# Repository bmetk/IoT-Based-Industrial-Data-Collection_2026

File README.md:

# COMPACT-MAPS
Machine Analizator and Processor System

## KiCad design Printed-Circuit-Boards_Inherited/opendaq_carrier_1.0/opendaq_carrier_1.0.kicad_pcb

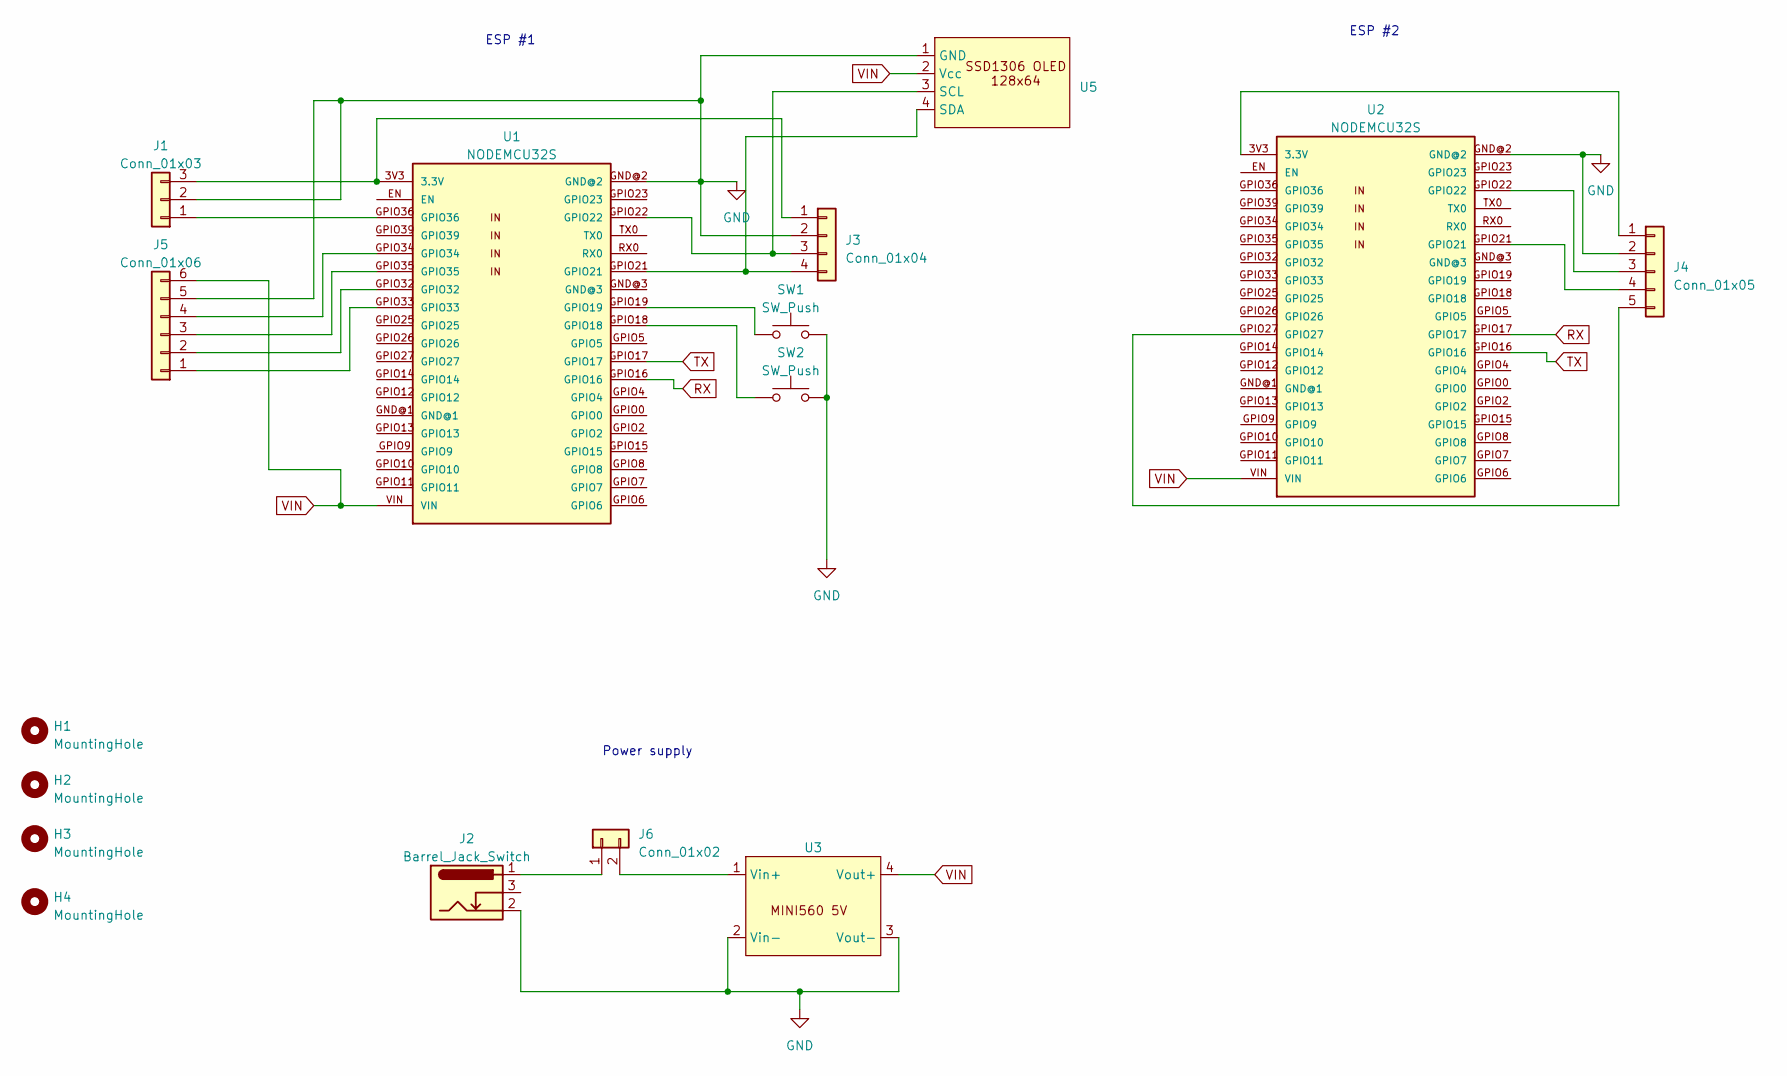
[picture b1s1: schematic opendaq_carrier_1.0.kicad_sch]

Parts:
H1, H2, H3, H4: MountingHole; MountingHole_3.2mm_M3_DIN965_Pad
J1: Conn_01x03; JST_XH_S3B-XH-A_1x03_P2.50mm_Horizontal
J2: Barrel_Jack_Switch; BarrelJack_Wuerth_6941xx301002
J3: Conn_01x04; JST_XH_S4B-XH-A_1x04_P2.50mm_Horizontal
J4: Conn_01x05; JST_XH_S5B-XH-A_1x05_P2.50mm_Horizontal
J5: Conn_01x06; JST_XH_S6B-XH-A_1x06_P2.50mm_Horizontal
J6: Conn_01x02; JST_XH_B2B-XH-A_1x02_P2.50mm_Vertical
SW1, SW2: SW_Push; SW_PUSH-12mm
U1, U2: NODEMCU32S
U3: MINI_560_buck
U5: SSD1306_OLED_128x64

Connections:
GND: J1.2, J2.2, J3.2, J4.2, J5.5, SW1.2, SW2.2, U1.GND@2, U2.GND@2, U3.2 (Vin-), U3.3 (Vout-), U5.1 (GND)
unnamed: J1.1, U1.GPIO36
unnamed: J1.3, J3.1, U1.3V3 (3.3V)
unnamed: J3.3, U1.GPIO22, U5.3 (SCL)
unnamed: J3.4, U1.GPIO21, U5.4 (SDA)
unnamed: J4.1, U2.3V3 (3.3V)
unnamed: J4.3, U2.GPIO22
unnamed: J4.4, U2.GPIO21
unnamed: J4.5, U2.GPIO27
unnamed: J5.1, U1.GPIO33
unnamed: J5.2, U1.GPIO32
unnamed: J5.3, U1.GPIO35
unnamed: J5.4, U1.GPIO34
unnamed: J2.1, J6.1
unnamed: J6.2, U3.1 (Vin+)
unnamed: SW1.1, U1.GPIO19
unnamed: SW2.1, U1.GPIO18
RX: U1.GPIO16, U2.GPIO17
TX: U1.GPIO17, U2.GPIO16
VIN: J5.6, U1.VIN, U2.VIN, U3.4 (Vout+), U5.2 (Vcc)

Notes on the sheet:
Power supply
ESP #1
ESP #2

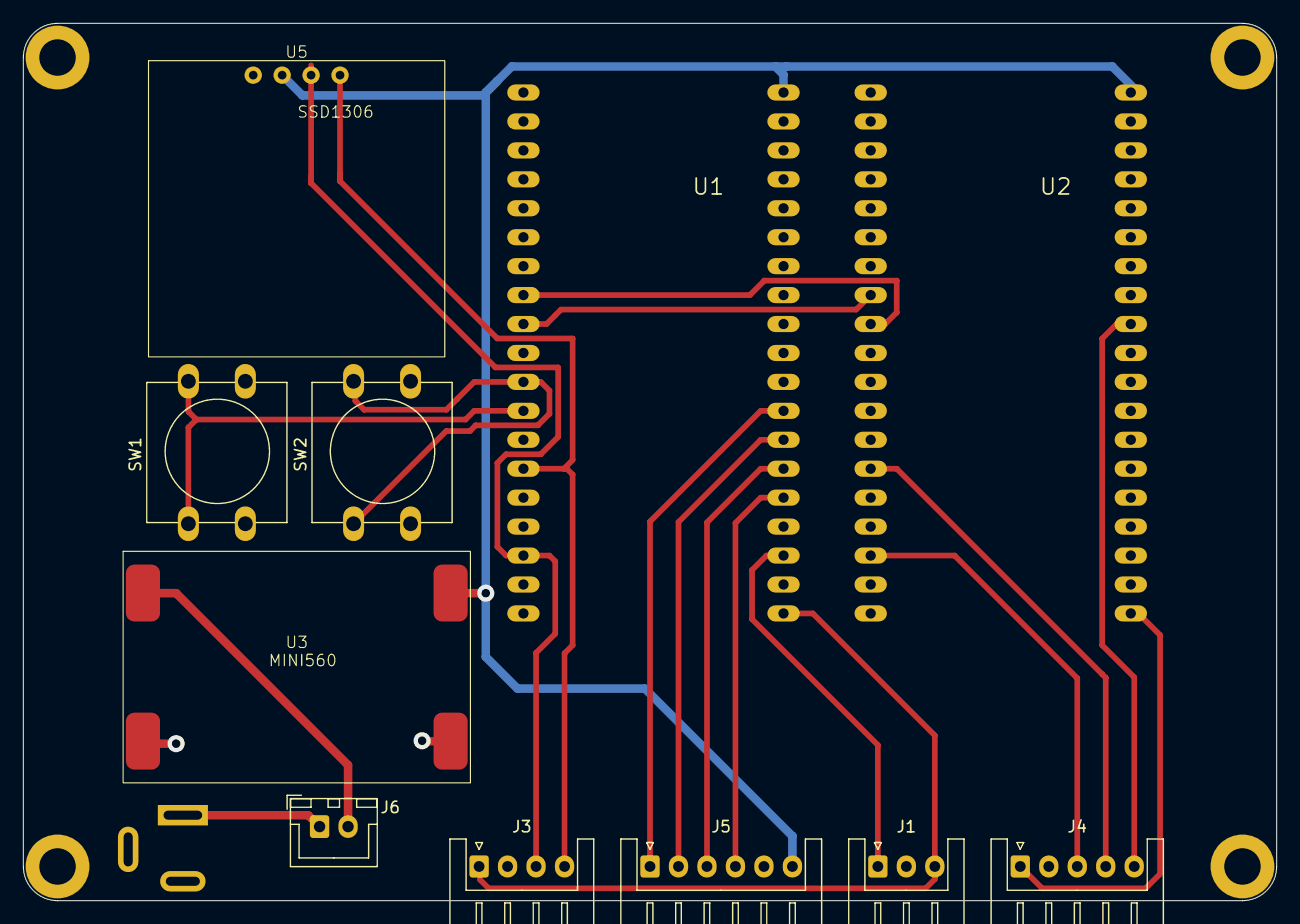
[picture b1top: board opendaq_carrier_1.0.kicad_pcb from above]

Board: 2 copper layers, 110.0 x 77.0 mm, 16 parts (1 on the bottom side), 20 nets.

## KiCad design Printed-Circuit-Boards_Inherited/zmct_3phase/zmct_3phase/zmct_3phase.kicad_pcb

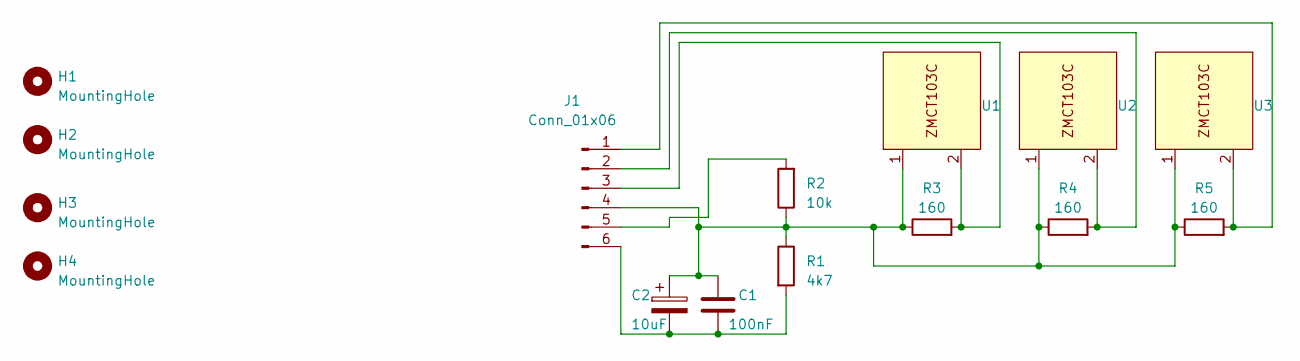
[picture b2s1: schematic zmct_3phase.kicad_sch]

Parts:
C1: 100nF; C_Disc_D3.8mm_W2.6mm_P2.50mm
C2: 10uF; CP_Radial_D4.0mm_P2.00mm
H1, H2, H3, H4: MountingHole; MountingHole_3.2mm_M3_DIN965_Pad
J1: Conn_01x06; JST_XH_S6B-XH-A_1x06_P2.50mm_Horizontal
R1: 4k7; R_Axial_DIN0207_L6.3mm_D2.5mm_P7.62mm_Horizontal
R2: 10k; R_Axial_DIN0207_L6.3mm_D2.5mm_P7.62mm_Horizontal
R3, R4, R5: 160; R_Axial_DIN0207_L6.3mm_D2.5mm_P7.62mm_Horizontal
U1, U2, U3: ZMCT103C

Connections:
unnamed: J1.1, R5.2, U3.2
unnamed: J1.2, R4.2, U2.2
unnamed: J1.3, R3.2, U1.2
unnamed: C1.1, C2.1, J1.4, R1.1, R2.1, R3.1, R4.1, R5.1, U1.1, U2.1, U3.1
unnamed: J1.5, R2.2
unnamed: C1.2, C2.2, J1.6, R1.2

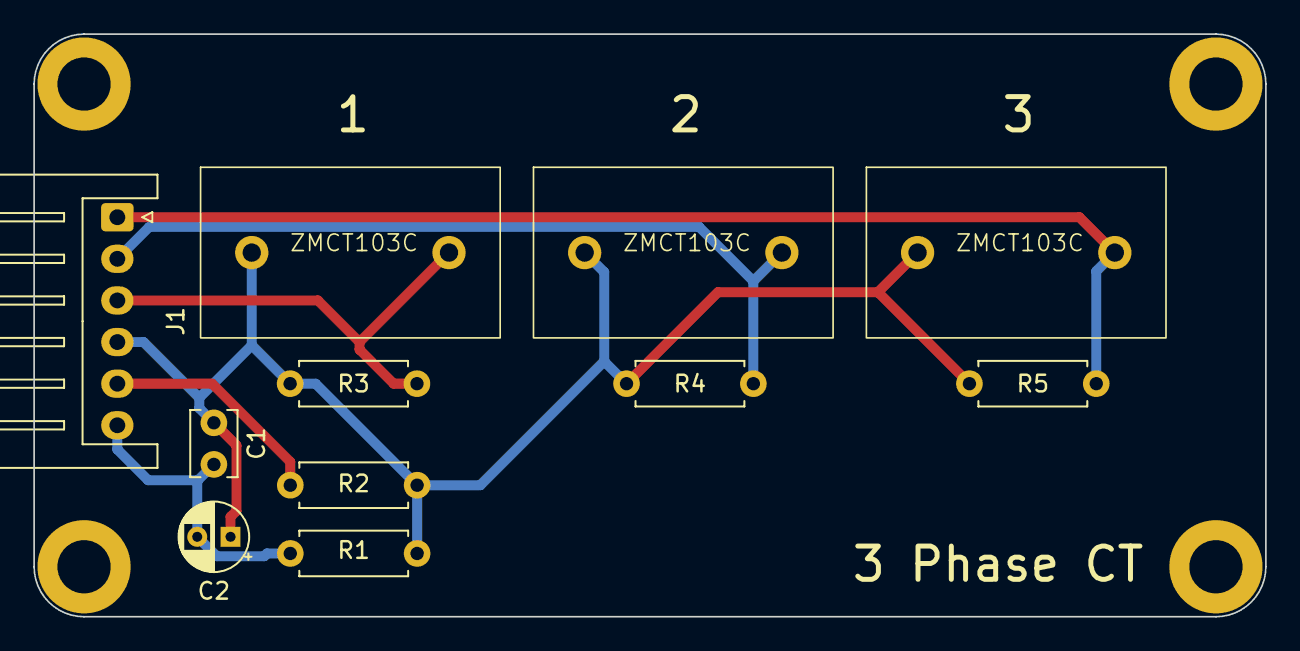
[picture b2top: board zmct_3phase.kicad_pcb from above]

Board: 2 copper layers, 74.0 x 35.0 mm, 15 parts (0 on the bottom side), 6 nets.

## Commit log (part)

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2026-03-15 working_backend_v1_without_ui
2026-03-16 Remove .env from .gitignore
2026-03-16 Added env file
2026-03-17 Refactor predict function to support multiple models
2026-03-17 Refactor predict function calls with additional parameters
2026-03-17 dashboard_development_v1
2026-03-18 dashboard_development_v2
2026-03-18 dashboard_development_v3
2026-03-22 ml_training_v1
2026-03-27 ml_training_v2
2026-03-31 esp32-[2]-vibration_v1 & backend adjust
2026-04-02 esp32-[1]-build_v1
2026-04-06 esp32-[1]-menu_v1
2026-04-10 esp1_and_esp2_build_v2
2026-04-14 simulator_and_esp1_build_v2
2026-04-15 esp1-menu_build_v3
2026-04-16 esp1_and_esp2_statuses_added_to_homepage
2026-04-21 dashboard_develpoment_v3.5
2026-04-22 simulator_fix_v1
2026-05-05 commenting_ESP1_and_ESP2_codes
2026-05-06 dashboard_build_v3
2026-05-09 dashboar_simulator_backend_build_v4
2026-05-10 download_service_added
2026-05-17 simulator_build_v5
2026-05-20 simulator_build_v6
2026-05-21 lathe02-code_v1
2026-05-24 simulator-fix_for-ml_v1
2026-05-25 simulator-fix_and_dashboard-upgrade_v2
2026-05-29 experimental-page_hotfix_v1
2026-05-29 experimental-page_hotfix_v2
2026-05-31 ui_hotfix_v1
2026-06-01 added_lathe02-code_and_lathe00-code
2026-06-04 commenting_and_added_inherited-files
2026-06-04 Updated project repository URL
    Updated project repository URL to the correct GitHub link.
2026-06-29 added-secondary-dbmember
